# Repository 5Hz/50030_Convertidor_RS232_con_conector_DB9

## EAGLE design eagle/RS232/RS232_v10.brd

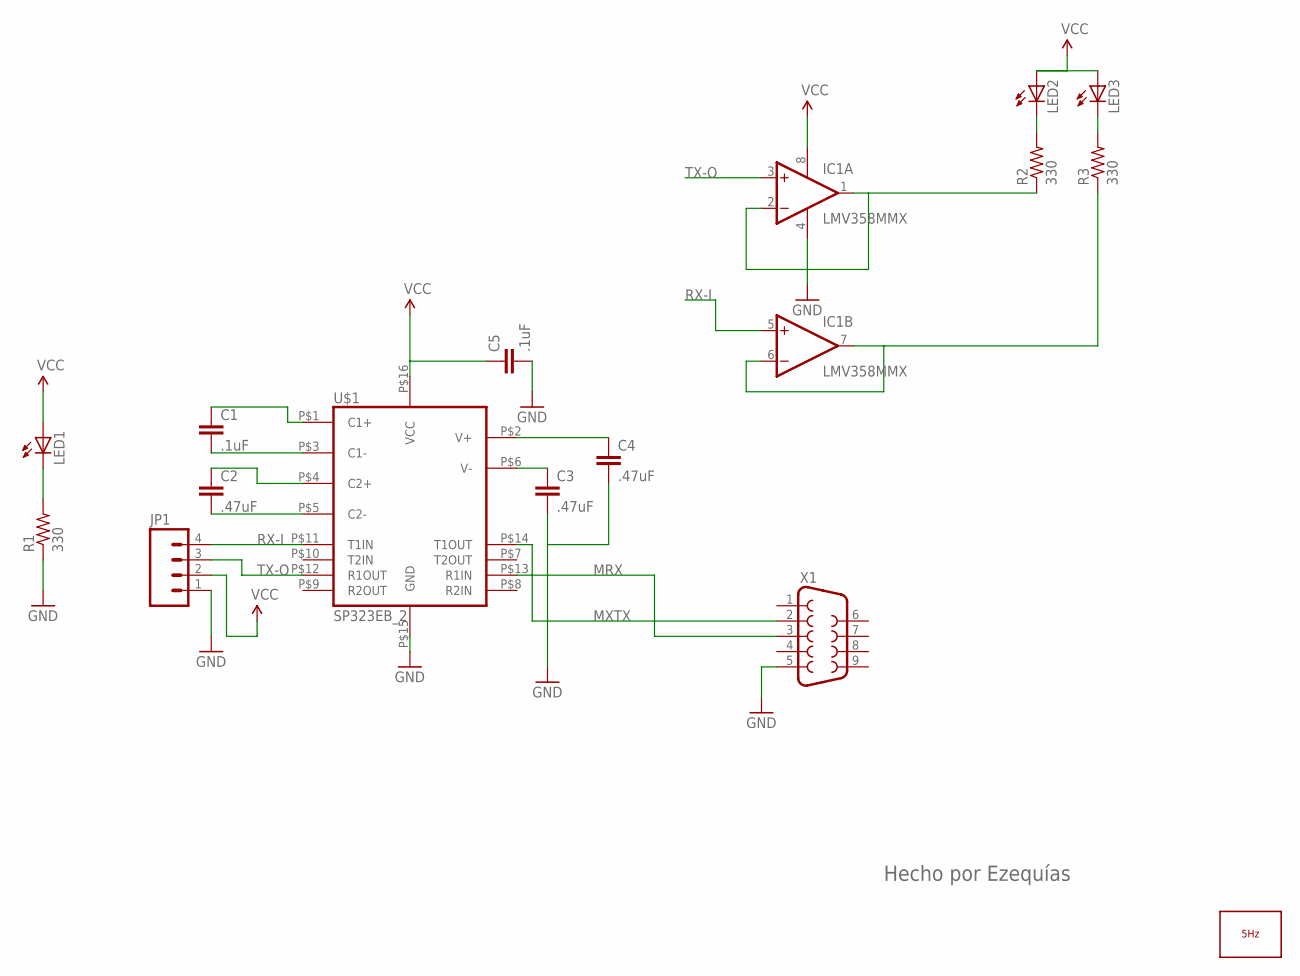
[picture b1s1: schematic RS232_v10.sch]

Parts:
C1, C5: .1uF; 0603-CAP
C2, C3, C4: .47uF; 0603-CAP
IC1: LMV358MMX; MSOP08
JP1: M04PTH; 1X04
LED1, LED2, LED3: LED0603; LED-0603
LOGO1: LOGO_5HZ_MAIN_15MM; 5HZ_LOGO_MAIN_15MM
R1, R2, R3: 330; 0603-RES
U$1: SP323EB_2; SSOP-16
X1: DB9FEMALE; DB9

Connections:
GND: C3.2, C4.2, C5.2, IC1.4 (V-), JP1.1, R1.1, U$1.P$15 (GND), X1.5
MRX: U$1.P$13 (R1IN), X1.3
MXTX: U$1.P$14 (T1OUT), X1.2
unnamed: C1.1, U$1.P$1 (C1+)
unnamed: C1.2, U$1.P$3 (C1-)
unnamed: C2.1, U$1.P$4 (C2+)
unnamed: C2.2, U$1.P$5 (C2-)
unnamed: C3.1, U$1.P$6 (V-)
unnamed: C4.1, U$1.P$2 (V+)
unnamed: LED1.C, R1.2
unnamed: LED2.C, R2.2
unnamed: LED3.C, R3.2
unnamed: IC1.1 (OUT), IC1.2 (-IN), R2.1
unnamed: IC1.6 (-IN), IC1.7 (OUT), R3.1
RX-I: IC1.5 (+IN), JP1.4, U$1.P$11 (T1IN)
TX-O: IC1.3 (+IN), JP1.3, U$1.P$12 (R1OUT)
VCC: C5.1, IC1.8 (V+), JP1.2, LED1.A, LED2.A, LED3.A, U$1.P$16 (VCC)

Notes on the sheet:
Hecho por Ezequías

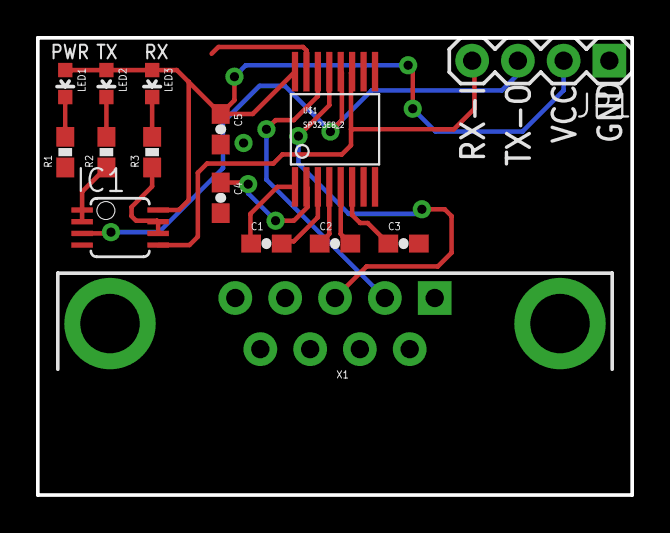
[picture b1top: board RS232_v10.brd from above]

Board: 2 copper layers, 33.0 x 25.4 mm, 16 parts (1 on the bottom side), 17 nets.

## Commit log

2014-01-10 creación
